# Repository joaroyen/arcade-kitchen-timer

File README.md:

# Arcade Kitchen Timer

The Arcade Kitchen Timer Mini is my first attempt at designing and developing a product using electronics, programming and 3D modelling. See [Wiki](https://github.com/joaroyen/arcade-kitchen-timer/wiki) for details about the project.

> PS: Don't expect much activity in this repository after it is published.

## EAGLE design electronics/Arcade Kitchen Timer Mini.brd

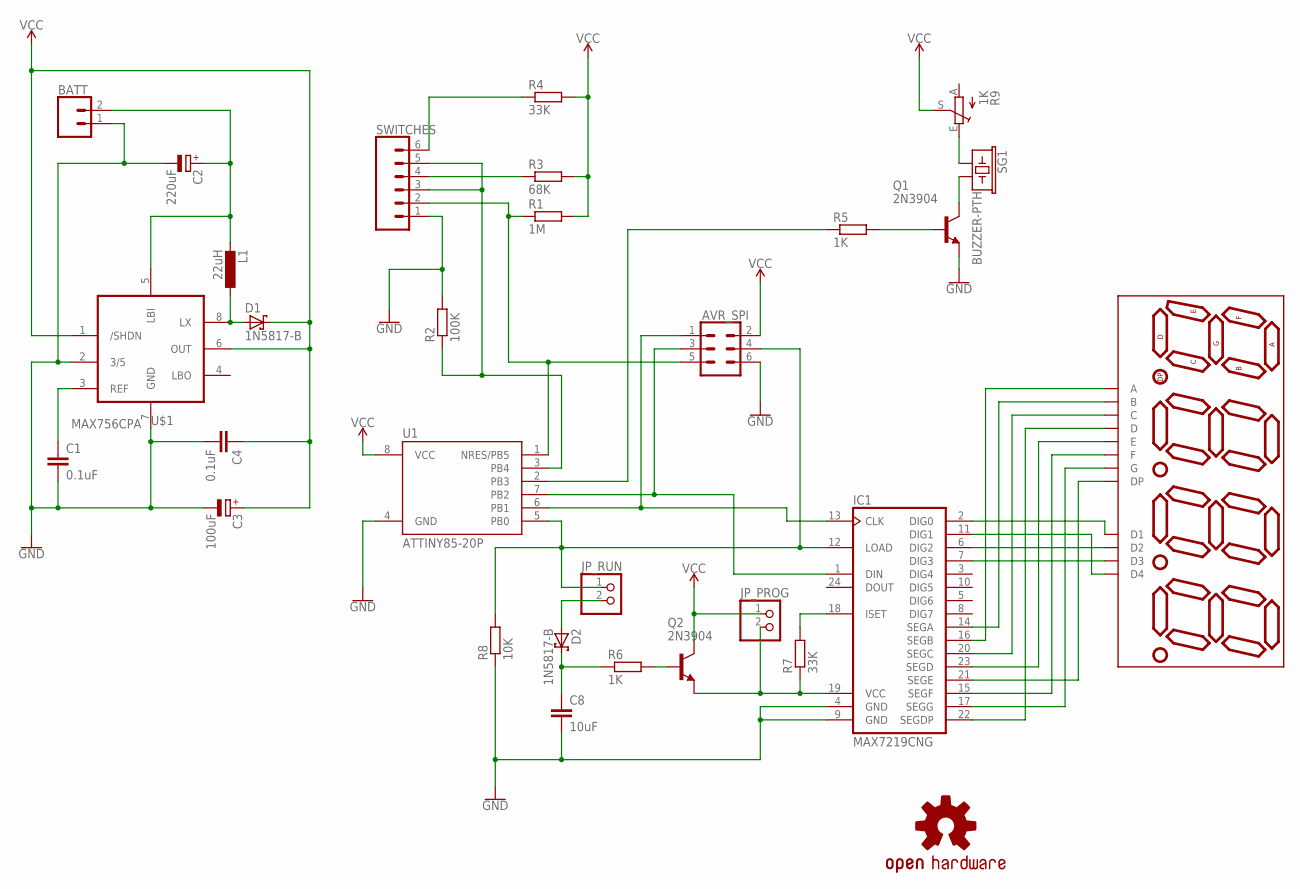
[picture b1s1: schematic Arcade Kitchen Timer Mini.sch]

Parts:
AVR_SPI: CONN_03X2SHROUD; 2X3-SHROUDED
BATT: CONN_02POLAR; MOLEX-1X2
C1, C4: 0.1uF; C050-035X075
C2: 220uF; E2,5-7
C3: 100uF; E2,5-6
C8: 10uF; C050-035X075
D1, D2: 1N5817-B; DO41-7.6
DISP1: ATA8041ARBJ; 7-SEGMENT-4DIGIT-20MM
IC1: MAX7219CNG; DIL24-3
JP_PROG: PINHD-1X2; 1X02
JP_RUN: PINHD-1X2; 1X02
L1: 22uH; 6000-XXXX-RC
LOGO1: OSHW-LOGOM; OSHW-LOGO-M
Q1, Q2: 2N3904; TO92
R1: 1M; 0207/10
R2: 100K; 0207/10
R3: 68K; 0207/10
R4, R7: 33K; 0207/10
R5, R6: 1K; 0207/10
R8: 10K; 0207/10
R9: 1K; B25P
SG1: BUZZER-PTH; BUZZER-12MM
SWITCHES: CONN_06POLAR; MOLEX-1X6
U1: ATTINY85-20P; PDIP08_300MIL
U$1: MAX756CPA; DIL08

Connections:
GND: AVR_SPI.6, BATT.1, C1.2, C2.-, C3.-, C4.2, C8.2, IC1.4 (GND), IC1.9 (GND), Q1.3 (E), R2.2, R8.1, SWITCHES.1, U1.4 (GND), U$1.2 (3/5), U$1.7 (GND)
unnamed: D1.A, L1.1, U$1.8 (LX)
unnamed: R5.1, U1.2 (PB3)
unnamed: R3.1, SWITCHES.4
unnamed: Q1.2 (B), R5.2
unnamed: AVR_SPI.5, R1.1, SWITCHES.2, U1.1 (NRES/PB5)
unnamed: D2.A, JP_RUN.2
unnamed: R4.1, SWITCHES.6
unnamed: Q2.2 (B), R6.2
unnamed: C1.1, U$1.3 (REF)
unnamed: Q1.1 (C), SG1.- (2)
unnamed: R9.E, SG1.+ (1)
unnamed: AVR_SPI.3, IC1.1 (DIN), U1.7 (PB2)
unnamed: IC1.18 (ISET), R7.2
unnamed: C8.1, D2.C, R6.1
unnamed: AVR_SPI.1, IC1.13 (CLK), U1.6 (PB1)
unnamed: AVR_SPI.4, IC1.12 (LOAD), JP_RUN.1, R8.2, U1.5 (PB0)
unnamed: IC1.19 (VCC), JP_PROG.2, Q2.3 (E), R7.1
unnamed: DISP1.11 (A), IC1.16 (SEGB)
unnamed: DISP1.7 (B), IC1.14 (SEGA)
unnamed: DISP1.4 (C), IC1.20 (SEGC)
unnamed: DISP1.2 (D), IC1.22 (SEGDP)
unnamed: DISP1.1 (E), IC1.23 (SEGD)
unnamed: DISP1.10 (F), IC1.15 (SEGF)
unnamed: DISP1.5 (G), IC1.17 (SEGG)
unnamed: DISP1.3 (DP), IC1.21 (SEGE)
unnamed: DISP1.12 (D1), IC1.2 (DIG0)
unnamed: DISP1.9 (D2), IC1.6 (DIG2)
unnamed: DISP1.8 (D3), IC1.7 (DIG3)
unnamed: DISP1.6 (D4), IC1.11 (DIG1)
unnamed: BATT.2, C2.+, L1.2, U$1.5 (LBI)
unnamed: R2.1, SWITCHES.3, SWITCHES.5, U1.3 (PB4)
VCC: AVR_SPI.2, C3.+, C4.1, D1.C, JP_PROG.1, Q2.1 (C), R1.2, R3.2, R4.2, R9.S, U1.8 (VCC), U$1.1 (/SHDN), U$1.6 (OUT)

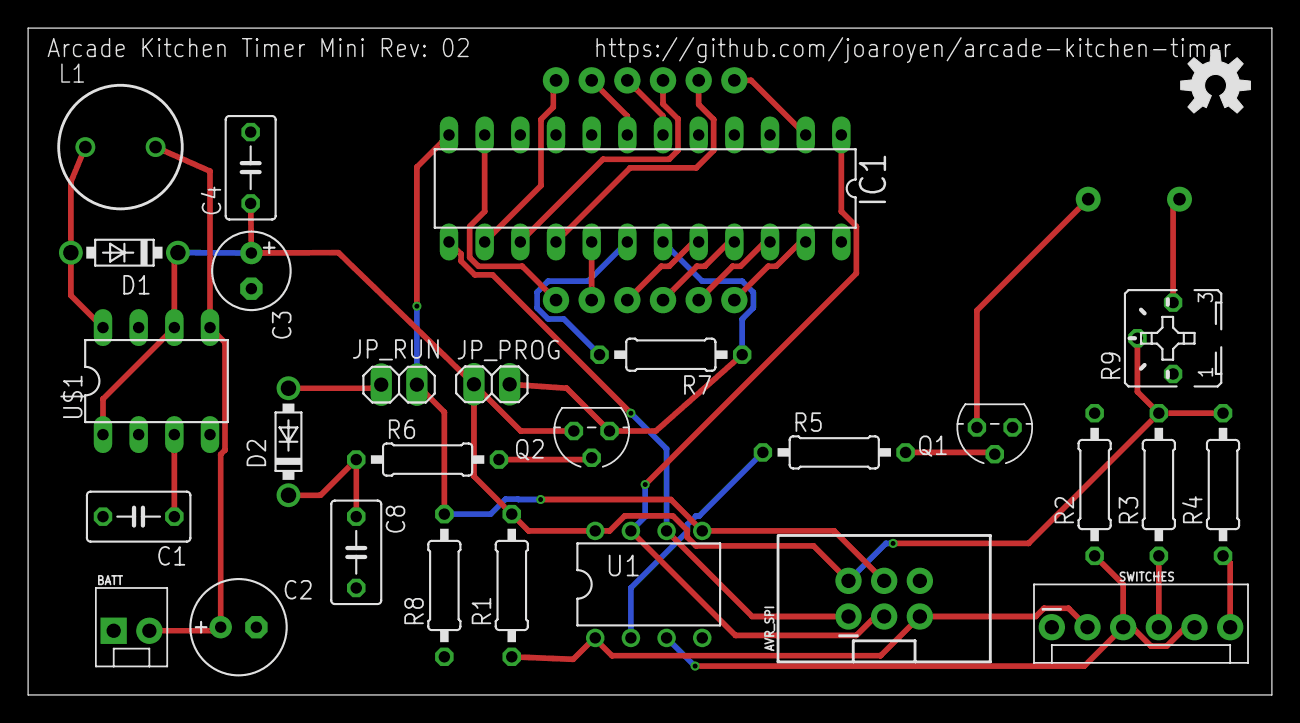
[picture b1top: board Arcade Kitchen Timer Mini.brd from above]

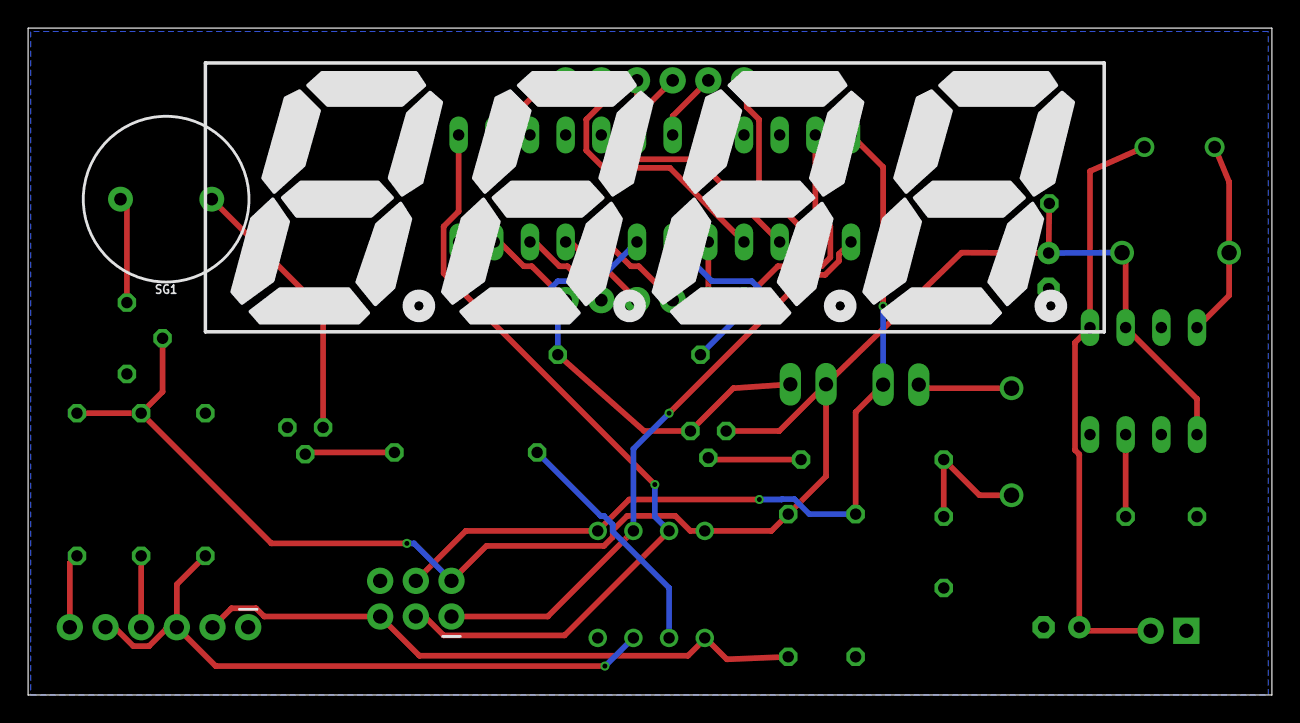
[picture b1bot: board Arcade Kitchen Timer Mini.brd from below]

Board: 2 copper layers, 88.6 x 47.5 mm, 30 parts (2 on the bottom side), 33 nets.

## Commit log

2017-12-25 Set theme jekyll-theme-slate
2017-12-25 Placeholder for GitHub pages
2017-12-25 Deleting missplaced GitHub pages files
2017-12-25 Testing images in GitHub wiki
2017-12-25 Renderer of open enclosure
2017-12-25 Changed possition and lighting
2017-12-26 Adding enclosure 3D model files
2017-12-26 Added electronics files
2017-12-28 Updated documentation with images
2017-12-30 Arcate Kitchen Timer Mini sketch
2017-12-30 Moved into separate Mini folder to support Arduino editor
2017-12-30 Hacked audio frequency tuning sketch

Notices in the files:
parts and their libraries:
SparkFun-Connectors: Licensing: Creative Commons ShareAlike 4.0 International - https://creativecommons.org/licenses/by-sa/4.0
